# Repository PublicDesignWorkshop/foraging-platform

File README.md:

#Foraging platform

This repository contains the software and hardware designs to produce a low-power datalogger for remote monitoring fruit ripeness. Included in this repository is:

1. Arduino code for the datalogger itself
2. schematics and PCB designs for custom, low-power arduino variants in  Eagle and Gerber format
3. Enclosure models in sketchup and .STL format for 3D printing
4. PDF of lids to fit the enclosures that can be laser-cut

###Goals
This platform is meant to be deployed autonomously on fruit trees while their fruit ripens. It offers a way for urban foragers to monitor remotely many trees, and lessen their reliance on volunteers or manually checking the fruit status on trees across large distances over long durations. It uses two different kinds of sensors to monitor the fruit’s ripeness. The first is a bend sensor attached to a branch that will bear fruit to represent the ripeness of the tree. In the second, a stretch sensor is placed between two branches. In each case, as the fruit grows, the branch bearing that fruit bends, providing a changing reading to our sensors.

###Current Iteration
Right now, the platform uses a real-time clock module to wake a custom Arduino board from a deep, energy-saving sleep mode and then logs the current bend data to a MicroSD card. In this configuration, the board has lasted over a month deployed in a tree during Summer 2015, reading every 12 hours. Decreasing the frequency of readings should enable much longer deployment times. Currently (Summer 2016) we are testing new sensors reading every 23 hours.

###Photos

###Technical Details
[Bill of Materials](https://docs.google.com/spreadsheets/d/1Vs3_GVGOHFVuYa3o1AHFbKYVgtYUHnmqFQ5do5olbm8/edit#gid=990807043) - includes notes for datalogging, WiFi and cellular versions

####Hardware and software dependencies

Hardware:

* [SparkFun DeadOn RTC Breakout - DS3234](https://www.sparkfun.com/products/10160)
* [LC Tech Mini SD Card Module](http://www.chinalctech.com/index.php?_m=mod_product&_a=view&p_id=646)

Software Libraries:

* [SD Library](https://www.arduino.cc/en/Reference/SD)
* [ManiacBug's fork of RTClib](https://github.com/maniacbug/RTClib)
* [Rodan's DS3234 Library](https://github.com/rodan/ds3234)
* [Enerlib](http://playground.arduino.cc/Code/Enerlib)

####Potential future comm/sensor choices
Cell phone breakout board and pay-as-you-go SIM card options:

* https://www.adafruit.com/products/1963
* https://www.adafruit.com/products/1946

Inexpensive WiFi breakout board:

* https://www.sparkfun.com/products/13678

21 Sensors under $2:

* http://randomnerdtutorials.com/21-arduino-modules-you-can-buy-for-less-than-2/

###Problems and Issues
#####Accuracy Issues
There are a couple of obvious issues with this setup. The first is that the weight of fruit is the proxy for ripeness. This is not as much of a problem as it could be, because knowing when fruit gets heavy means that volunteer resources could be used to check on it for more detailed results. Additionally, we are experimenting with combinations of gas sensors to more properly detect ripeness itself.
#####Technical Issues
By far the most limiting issues we’ve come across have been technical. Detecting a bend is not very difficult, and building out a low-power sensor board as well as the industrial design planning to deploy the platform has been relatively straightforward. However, the initial vision of a wireless, long-term deployment has been difficult. Even sensing and sending bend every 24 hours doesn’t come very close to the long-term deployment envisioned.

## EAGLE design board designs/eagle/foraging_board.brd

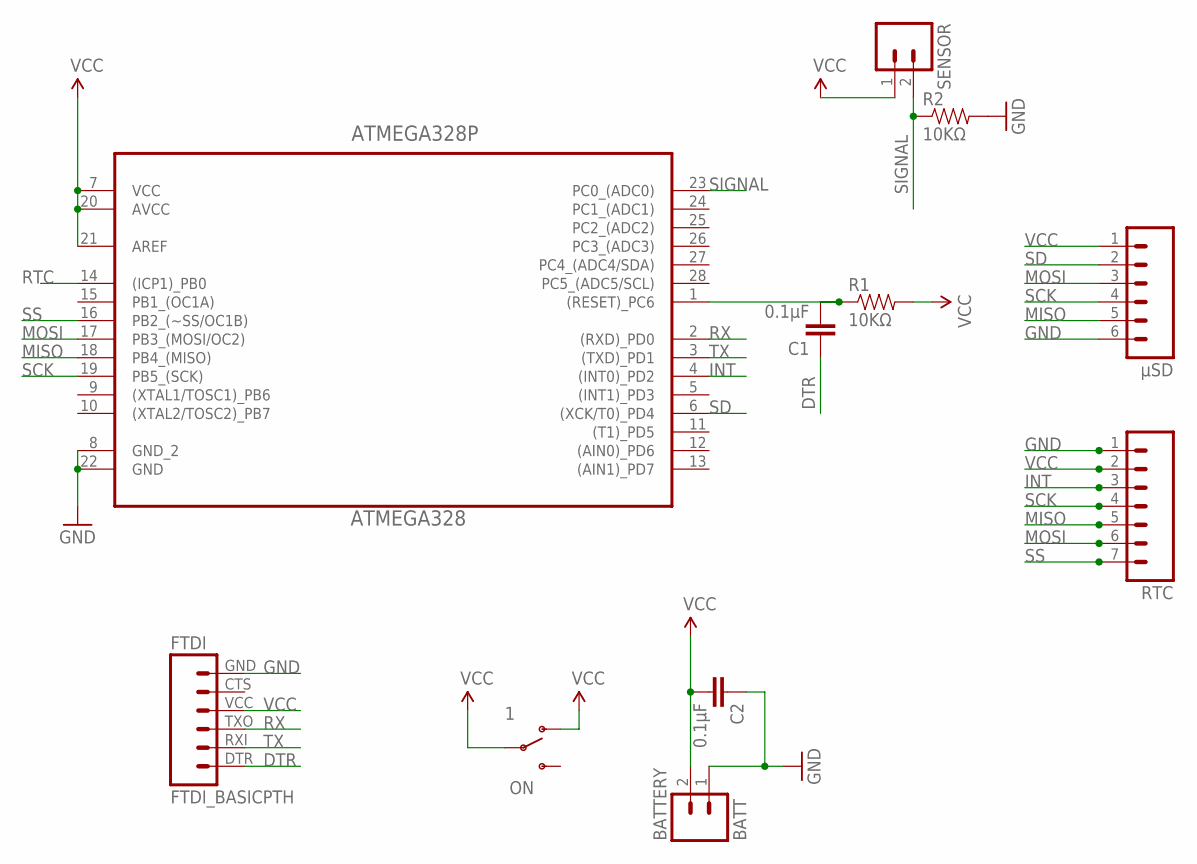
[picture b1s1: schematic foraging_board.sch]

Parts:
ATMEGA328P: ATMEGA328; DIP254P762X457-28
BATTERY: BATT; JST-2-PTH-NS
C1, C2: 0.1µF; CAP-PTH-SMALL-KIT
FTDI: FTDI_BASICPTH; FTDI_BASIC
ON: 1; SWITCH-SPDT_KIT
R1, R2: 10KΩ; AXIAL-0.3EZ
RTC: M07LONGPADS; 1X07_LONGPADS
SENSOR: M02PTH; 1X02
µSD: M06LONGPADS; 1X06_LONGPADS

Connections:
DTR: C1.1, FTDI.DTR (1)
GND: ATMEGA328P.8 (GND_2), ATMEGA328P.22 (GND), BATTERY.1, C2.1, FTDI.GND (6), R2.P$2 (2), RTC.1, µSD.6
INT: ATMEGA328P.4 ((INT0)_PD2), RTC.3
MISO: ATMEGA328P.18 (PB4_(MISO)), RTC.5, µSD.5
MOSI: ATMEGA328P.17 (PB3_(MOSI/OC2)), RTC.6, µSD.3
unnamed: ATMEGA328P.1 ((RESET)_PC6), C1.2, R1.P$1 (1)
RTC: ATMEGA328P.14 ((ICP1)_PB0)
RX: ATMEGA328P.2 ((RXD)_PD0), FTDI.TXO (3)
SCK: ATMEGA328P.19 (PB5_(SCK)), RTC.4, µSD.4
SD: ATMEGA328P.6 ((XCK/T0)_PD4), µSD.2
SIGNAL: ATMEGA328P.23 (PC0_(ADC0)), R2.P$1 (1), SENSOR.2
SS: ATMEGA328P.16 (PB2_(~SS/OC1B)), RTC.7
TX: ATMEGA328P.3 ((TXD)_PD1), FTDI.RXI (2)
VCC: ATMEGA328P.7 (VCC), ATMEGA328P.20 (AVCC), ATMEGA328P.21 (AREF), BATTERY.2, C2.2, FTDI.VCC (4), ON.1 (O), ON.2, R1.P$2 (2), RTC.2, SENSOR.1, µSD.1

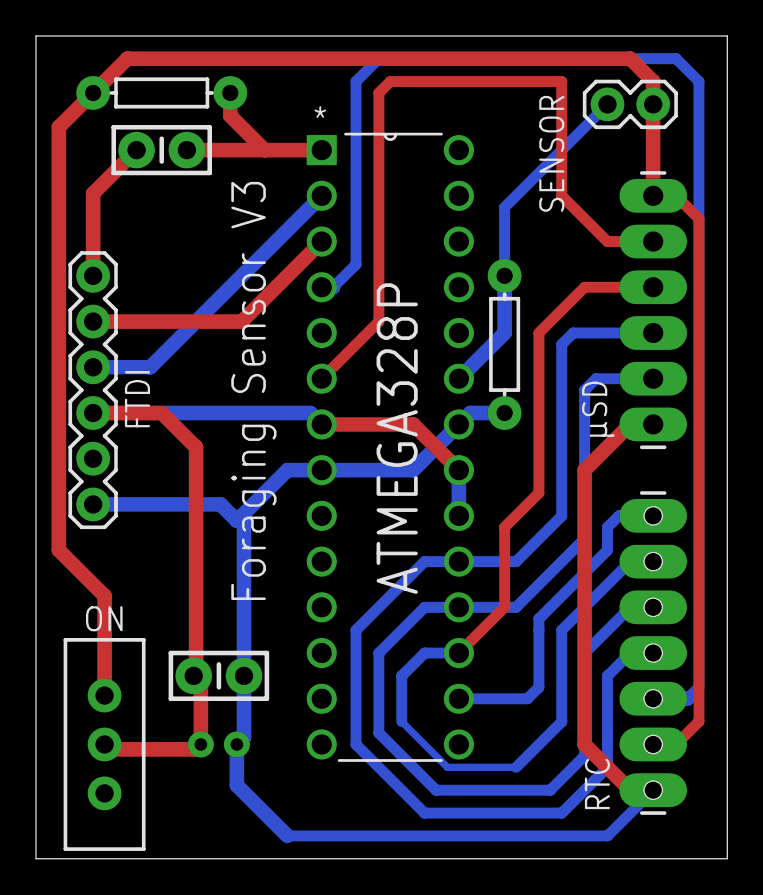
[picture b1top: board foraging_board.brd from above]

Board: 2 copper layers, 38.4 x 45.7 mm, 11 parts (0 on the bottom side), 13 nets.

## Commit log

2016-06-22 First commit: arduino file, Eagle and gerber PCB and schematic files, and casing designs
2016-06-22 remove hidden file
2016-06-22 first readme
2016-06-22 fix typo in readme
2016-06-22 fix typo in readme again
2016-06-22 break out cases so no single file has two sizes
2016-07-05 New case design files, updated README
2016-07-05 Heading structure modifications
2016-07-05 remove extraneous close paren
2016-07-06 fix image link in readme
2016-07-06 typo fix
2016-07-06 formatting dependencies list
2016-07-06 more dependencies formatting
2016-07-06 header sizes bugging me a little
2017-04-04 Adding data from 2015 and 2016 deployments

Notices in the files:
parts and their libraries:
SparkFun-Capacitors: Licensing: CC v3.0 Share-Alike You are welcome to use this library for commercial purposes.
